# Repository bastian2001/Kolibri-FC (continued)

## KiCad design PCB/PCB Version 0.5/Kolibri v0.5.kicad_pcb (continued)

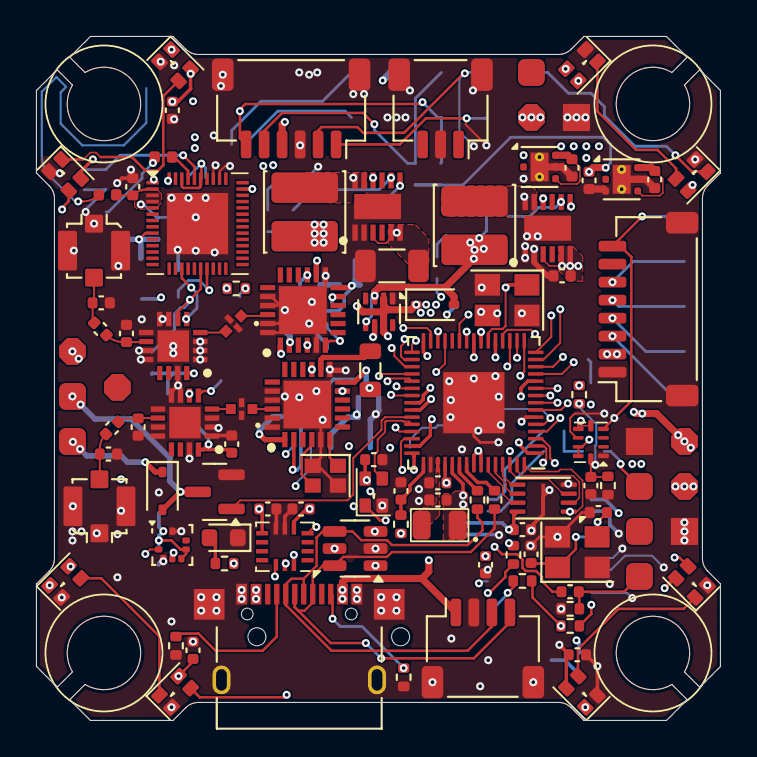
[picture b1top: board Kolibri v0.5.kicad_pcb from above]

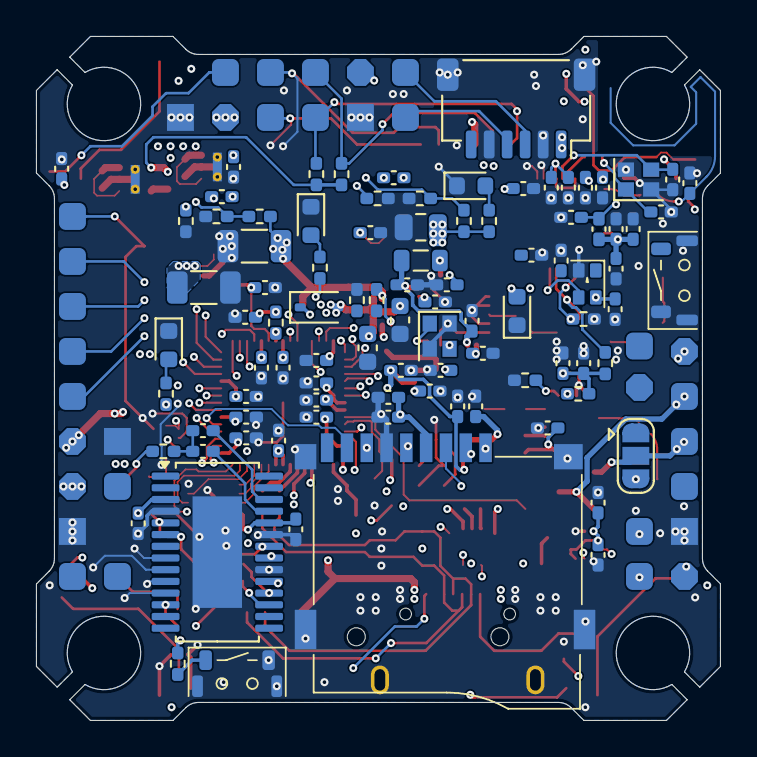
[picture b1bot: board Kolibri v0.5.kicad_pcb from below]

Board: 8 copper layers, 38.0 x 38.0 mm, 216 parts (114 on the bottom side), 144 nets.

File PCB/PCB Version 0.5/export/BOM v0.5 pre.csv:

Reference,Value,LCSC #,Datasheet,Footprint,Qty,DNP
"C1,C3,C4,C5,C6,C7,C8,C9,C10,C16,C17,C18,C19,C20,C21,C22,C23,C24,C25,C26,C27,C28,C33,C34,C40,C44,C45,C60,C62,C65,C67,C70,C71,C74,C76,C85,C86",100n,C110251,~,Capacitor_SMD:C_0402_1005Metric,37,
"C2,C11,C12,C13",4.7u,C368809,~,Capacitor_SMD:C_0402_1005Metric,4,
"C14,C15,C38,C39,C79,C80",15p,C880657,~,Capacitor_SMD:C_0402_1005Metric,6,
"C29,C30,C35,C50,C53,C73,C75,C81,C82,C83,C84",1u,0402 + 0603 alles da,~,Capacitor_SMD:C_0402_1005Metric,11,
"C31,C42,C43,C55,C56",10n,0402 + 0603 alles da,~,Capacitor_SMD:C_0402_1005Metric,6,
"C32,C37",1.5p,C76958,~,Capacitor_SMD:C_0402_1005Metric,2,
"C36,C77,C78",10u,ist da,~,Capacitor_SMD:C_0402_1005Metric,3,
"C41,C61",470n,ist da,~,Capacitor_SMD:C_0402_1005Metric,2,
"C46,C57",47p,ist da,~,Capacitor_SMD:C_0402_1005Metric,2,
"C49,C54",220p,C7503514,~,Capacitor_SMD:C_0402_1005Metric,2,
"C51,C52,C58,C59",DNF,-,~,Capacitor_SMD:C_0402_1005Metric,4,
"C63,C64",1u,0402 + 0603 alles da,~,Capacitor_SMD:C_0603_1608Metric,2,
C66,47u,ist da,~,Capacitor_SMD:C_1206_3216Metric,1,
"C68,C69",2.2u,ist da,~,Capacitor_SMD:C_0805_2012Metric,2,
C72,22u,C602037,~,Capacitor_SMD:C_0805_2012Metric,1,
"D1,D2,D3,D4,D5,D6,D7,D8,D9,D11",~,30x C5349954,https://www.lcsc.com/datasheet/lcsc_datasheet_2410121315_XIN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,Kolibri custom:WS2812B_1615,10,
"D10,D12,D13",1N4148WS,C917117,https://www.vishay.com/docs/85751/1n4148ws.pdf,Diode_SMD:D_SOD-323,3,
"FL1,FL2",2450FM07D0034T,"Muss geklaut werden: C2917726, C6054595, C2651081",https://www.mouser.co.uk/datasheet/2/611/2450FM07D0034-1375634.pdf,SamacSys_Parts:2450FM07D0034T,2,
"IC1,IC3",SX1280IMLTRT,ist da,https://datasheet.datasheetarchive.com/originals/distributor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,SamacSys_Parts:QFN50P400X400X100-25N-D,2,
"IC2,IC4",RFX2401C,AT2401 ist da,,SamacSys_Parts:QFN50P300X300X60-17N-D,2,
"IC5,IC6",LMR38025SDRRR,ist da,https://www.ti.com/lit/ds/symlink/lmr38025.pdf?ts=1711363220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,SamacSys_Parts:SON50P300X300X80-13N,2,
J1,USB_C_Receptacle_USB2.0_16P,10x C963217,https://www.usb.org/sites/default/files/documents/usb_type-c.zip,Kolibri custom:USB-C SMD+THT,1,
J2,Conn_01x04_MountingPin,C2905006,~,Connector_JST:JST_SH_SM04B-SRSS-TB_1x04-1MP_P1.00mm_Horizontal,1,
"J3,J4",Conn_Coaxial_Small,C5137195,~,Connector_Coaxial:U.FL_Molex_MCRF_73412-0110_Vertical,2,
J5,Conn_01x08_MountingPin,C7433429,~,Connector_JST:JST_SH_SM08B-SRSS-TB_1x08-1MP_P1.00mm_Horizontal,1,
"J6,J7",Conn_01x06_MountingPin,ist da,~,Connector_JST:JST_SH_SM06B-SRSS-TB_1x06-1MP_P1.00mm_Horizontal,2,
J8,Conn_01x03_MountingPin,C7433424,~,Connector_JST:JST_SH_SM03B-SRSS-TB_1x03-1MP_P1.00mm_Horizontal,1,
J9,Micro_SD_Card_Det1,ist da,https://datasheet.lcsc.com/lcsc/2110151630_XKB-Connectivity-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,Kolibri custom:Micro SD Card (TF),1,
L1,3.3u,C42411119,~,,1,
L2,2.0n,ist da,~,Inductor_SMD:L_0402_1005Metric,1,
L3,3.0n,ist da/s.u.,~,Inductor_SMD:L_0402_1005Metric,1,
L4,24n,C401493,~,Inductor_SMD:L_0402_1005Metric,1,
"L5,L6",15u,C5344252,~,Inductor_SMD:L_0402_1005Metric,2,
"L7,L8",4.7u,C520275,~,Inductor_SMD:L_Cenker_CKCS4020,2,
"P1,P2,P3,P4,P5,P6,P7,P8,P9,P10,P11,P12,P13,P14,P15,P16,P17",~,-,,Kolibri custom:Solder_Pad_rounded,17,
"P18,P19,P20,P21,P22",~,-,,Kolibri custom:Solder_Pad_rounded_dual,5,
"P23,P24,P25",~,-,,Kolibri custom:Solder_Pad_rect_dual,3,
"P26,P27",~,-,,Kolibri custom:Solder_Pad_rect,2,
"P28,P29,P30,P33,P34",~,-,,Kolibri custom:Solder_Pad_octa_dual,5,
"P31,P32",~,-,,Kolibri custom:Solder_Pad_octa,2,
Q1,BSS138,100x C5224263,https://www.onsemi.com/pub/Collateral/BSS138-D.PDF,Package_TO_SOT_SMD:SOT-23,1,
"R1,R2",27,0402 + 0603 alles da,~,Resistor_SMD:R_0402_1005Metric,2,
R3,33,C138002,~,Resistor_SMD:R_0402_1005Metric,1,
"R4,R21,R22,R23",1k,0402 + 0603 alles da,~,Resistor_SMD:R_0402_1005Metric,4,
"R5,R6",5.1k,0402 + 0603 alles da,~,Resistor_SMD:R_0402_1005Metric,2,
"R7,R8",6.8k,C2906876,~,Resistor_SMD:R_0402_1005Metric,2,
"R9,R10,R11,R12,R13",100k,0402 ist da,~,Resistor_SMD:R_0402_1005Metric,5,
R14,39k,C328318,~,Resistor_SMD:R_0402_1005Metric,1,
R15,40.2k,C2933097,~,Resistor_SMD:R_0402_1005Metric,1,
"R16,R20,R27",10k,0402 + 0603 alles da,~,Resistor_SMD:R_0402_1005Metric,3,
R17,22.6k,C321379,~,Resistor_SMD:R_0402_1005Metric,1,
R18,21.5k,0402 ist da,~,Resistor_SMD:R_0402_1005Metric,1,
R19,90.9k,0402 ist da,~,Resistor_SMD:R_0402_1005Metric,1,
"R24,R25",75,0402 + 0603 alles da,~,Resistor_SMD:R_0402_1005Metric,2,
R26,120k,-> 100k,~,Resistor_SMD:R_0402_1005Metric,1,
S1,Goertek SPL06-001,-> 3x C94049 (STMicro),,Kolibri custom:Goertek SPL06-001,1,
U1,RP2350A,10x C42411118,,Kolibri custom:QFN-60_EP_7x7_Pitch0.4mm,1,
U2,BMI270,2x C2836813,https://www.bosch-sensortec.com/media/boschsensortec/downloa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,Package_LGA:Bosch_LGA-14_3x2.5mm_P0.5mm,1,
U3,ESP32-U4WDH,2x C20622217,,Kolibri custom:QFN-48_EP_5x5_Pitch0.35mm,1,
U4,TPS2116DRL,ist da,https://www.ti.com/lit/ds/symlink/tps2116.pdf,Package_TO_SOT_SMD:SOT-583-8,1,
U5,AT7456E,10x C82351,,Package_SO:HTSSOP-28-1EP_4.4x9.7mm_P0.65mm_EP2.75x6.2mm,1,
U6,LP5912-3.3DRV,ist da,http://www.ti.com/lit/ds/symlink/lp5912.pdf,Package_SON:WSON-6-1EP_2x2mm_P0.65mm_EP1x1.6mm_ThermalVias,1,
U7,TPS746-3.3DRV,ist da,http://www.ti.com/lit/ds/symlink/lp5912.pdf,Package_SON:WSON-6-1EP_2x2mm_P0.65mm_EP1x1.6mm_ThermalVias,1,
U8,WE-TVS-824015043,ist da: C5380470,https://www.we-online.com/components/products/datasheet/8240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,Package_TO_SOT_SMD:SOT-23-6,1,
U9,TLV9002S_RUG_X2QFN,ist da,,Kolibri custom:Texas_X2QFN_RUG_10pin_1.5x2mm,1,
U10,W25Q16JVUXIQ,10x C2843335,http://www.winbond.com/resource-files/w25q32jv%20revg%200327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,Package_SON:Winbond_USON-8-1EP_3x2mm_P0.5mm_EP0.2x1.6mm,1,
"Y1,Y4",Crystal_GND24,s.u.,~,Crystal:Crystal_SMD_3225-4Pin_3.2x2.5mm,2,
Y2,Crystal_GND24,s.u.,~,Crystal:Crystal_SMD_2016-4Pin_2.0x1.6mm,1,
Y3,YXC OW7EL89CENUNFAYLC-52M,s.u.,https://www.sitime.com/support/resource-library/datasheets/s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,Oscillator:Oscillator_SMD_SiT_PQFN-4Pin_2.0x1.6mm,1,
,,,,,,
,,,,,,
,Crystals,,,,,
,12MHz 2520,C7294610,,,,
,Abra 12MHz 3225,C20625731,,,,
,27MHz 3225 von V2,C5261177,noch da,,,
,27Mhz 2016 Test,C18214311,,,,
,52MHz,C3034316,,,,
,40MHz,C37635335,,,,
,,,,,,
,,,,,,
,,,,,,
,Murata Inductor Pi,C703121,,,,
,Murata Coupling Cap,C77177,,,,
,Button,C530669,noch da,,,

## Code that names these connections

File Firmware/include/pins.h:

#include "typedefs.h"

#define PIN_TX0 0 // UART0 / Serial1
#define PIN_RX0 1 // UART0 / Serial1
#define PIN_TX1 8 // UART1 / Serial2
#define PIN_RX1 9 // UART1 / Serial2
#define PIN_TX2 10 // SoftwareSerial
#define PIN_RX2 11 // SoftwareSerial

#define PIN_OSD_MISO 12
#define PIN_OSD_CS 13
#define PIN_OSD_SCLK 14
#define PIN_OSD_MOSI 15

#define PIN_GYRO_INT1 16
#define PIN_GYRO_CS 17
#define PIN_GYRO_SCLK 18
#define PIN_GYRO_SDX 19

#define PIN_SD_DAT 2
#define PIN_SD_CMD 6
#define PIN_SD_SCLK 7

#define PIN_SDA0 24
#define PIN_SCL0 25

#define PIN_ADC_CURRENT 28
#define PIN_ADC_VOLTAGE 29

#define PIN_MOTORS 20 // pin at which the motor outputs start

#define PIN_SPEAKER 26
#define PIN_LEDS 27

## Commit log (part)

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2025-08-05 basic in flight tuning
2025-08-05 minor changes to OSD related classes
2025-08-05 basic working "OSD"
2025-08-05 nicer D gain shift
2025-08-06 math eval in numeric input
2025-08-06 German compatibility
2025-08-06 could not merge these...
2025-08-06 more debugging, doesn't work
2025-08-07 fix some things that were wrong with the return-to-x merge
2025-08-07 gyro at 400Hz
2025-08-07 fix speaker chirp
2025-08-11 get some intervals in order
2025-08-12 wip separation
2025-08-13 wip, to be tested
2025-08-13 semi-fix for blocked writes and disarm reason
2025-08-14 gen pidsum
2025-08-14 setpoint smoothing for lower control frequency
2025-08-18 store blackbox disarm reason
2025-08-18 Added more OSD elements; ready for testing
2025-08-18 !Disable Bidirectional DShot temporarily
    Because BL32 stupid doesn't allow update firmware
2025-08-28 minimize erase, write, read and init delays
    AM32 Configurator's timeouts regularly hit and made flashing impossible
    Resetting still hits the timeout
2025-08-28 voltage display with decimals
2025-08-29 remove logging duration
2025-08-29 More Blackbox elements (#109)
    Added the following blackbox items
    - Battery voltage whenever it is sampled (10Hz)
    - PID sum (can also be generated)
    - RC link statistics (RSSI etc.) whenever a Link statistics packet is received (usually 10Hz)
    simplified the leBytesToInt and leBytesToBigInt functions significantly so .slice is no longer needed
2025-08-31 wip untested
2025-09-10 Motor remapping (#114)
    - New setting to store the pins of the motors
    - 2 new MSP commands: SET/GET_MOTOR_LAYOUT (data: pins)
    - Remapping Wizard in the configurator
2025-09-11 wip working
    still need to implement retries, and change most components
2025-09-12 implement JS promises everywhere
    *where it is feasible, also omitting Blackbox for now
2025-09-12 promised blackbox
2025-09-13 fix elrs link stats recording
2025-09-13 fix blackbox file info display
2025-09-13 document JS sendCommand function
2025-09-13 JS promises for MSP commands (#116)
    sendCommand features a proper promise system now:
    - All the following parameters are adjustable
    - resolves when a packet with the same command is returned (custom function for checking returned packets possible to help with e.g. ping sequence numbers)
    - times out after 700ms
    - 3 attempts
    - internal data can be attached to the command, that the callback functions get passed, e.g. ping start time so that multiple pings don't jam up
2025-09-13 PID Boost OSD indicator
2025-09-13 Remove PIO speaker...
    it's been too long...
2025-09-13 finish removing speaker
2025-09-13 Clean up, remove PIO speaker (#118)
2025-09-13 Dump previous Tramp work
2025-09-15 wip tramp
2025-09-22 Tramp WIP
2025-09-23 hd -> hdx
2025-09-23 some light gui
2025-09-24 set frequency in configurator
2025-09-24 tunable by remote
2025-09-24 fix tuning initialize
2025-09-26 stronger background blue
2025-09-26 restyling header, better log scroll
2025-09-26 clean up home page slightly
2025-09-26 separate rate lines
2025-09-27 cargo update
2025-09-27 "fixing" something aka. compiler mimimi
2025-09-27 Configurator tweaks (#120)
    - some restyling
    - some code cleanup
    - update dependencies
2025-09-27 remove some hardware-only datasheets
2025-09-27 Move PCBs to separate Repo (#121)
2025-10-04 revert non-bidir
2025-10-04 make GPS work again
2025-10-15 IMU and Control lower update rate (#123)
    Reduces the update rate of IMU and control functions to 400Hz each. Also separates the control code into its own file for easier readability and maintenance.
2025-11-06 Implemented functions to save and load OSD configs from LittleFS
2025-11-11 making dependabot happy
2025-11-12 subframe wheel zooming and moving
2025-11-12 break out parsing into separate functions
2025-11-12 include offsets in loadedLog
2025-11-12 subframe touch move and zoom (untested)
2025-11-12 add control byte to sync
2025-11-12 wip header and data request
2025-11-15 reboot to bootloader on rightclick disconnect
2025-11-16 finished fast init and fast data req
    TODO JS scheduling
2025-11-16 wip, it opens start and end frame only for now
2025-11-16 working?
2025-11-16 removed a bunch of printf and sleeps
2025-11-17 blackbox viewer works
2025-11-18 export incomplete log with interpolation
2025-11-18 better selective drawing, motor output/RPM export
2025-11-18 Revise README for configurator updates
    Removed hardware features list and updated descriptions for various configurator features.
2025-11-18 make sync freq configurable
2025-11-18 Accelerated blackbox view (#124)
    - SYNC frames
    - polling individual frames
    - on demand download of blackbox log
    - export incomplete log by interpolating
    - show loading progress in configurator
2025-11-21 merged main into msp-displayport
2025-11-27 reading settings instead of hardcoded osd configuration
2025-11-29 wip icm implementation
2025-12-02 basic flash stuff
2025-12-03 FS creation
2025-12-04 more FS development, completely untested
2025-12-12 fix eraseBlock
2025-12-15 wip more static
2025-12-19 V0.6 implementation (#127)
    It's not all ideal, but it works generally. Kinda need this in other branches.
    - Barometer not further investigated, but doesn't work (probably hardware defect).
    - ABV still crashes the system sometimes (probably something wrong in the seek or read function of FlashFile)
    - code not completely refactored for 8kHz (PID gains, function splitting, etc.)
2025-12-19 clean up, fix MSP mix up
2025-12-27 some axes mixing around, untested
    most definitely some weird axes
2026-01-03 imu alignment mostly done
    todo accel part in imu fusion
2026-01-03 some fixing
2026-01-03 gyro only works
2026-01-03 wip (maybe working?)
2026-01-04 fix yaw jump at boot
    wait up to 50 ms to get a valid sample from the gyro
2026-01-04 simplified quaternion normalization
2026-01-04 I hate quaternions
    TODO optimization (like before)
2026-01-04 respect imu alignment during accel calibration
2026-01-05 optimizing IMU
    bench test yields 7.5-8.5 us per PID cycle now
2026-01-06 Fix sensor page interval
    Still crashing the browser sometimes. Maybe something with transferToOffscreen?
2026-01-06 adjust vAccel to new system
2026-01-06 fix when deleting a graph that was not the last
2026-01-06 UI for IMU alignment/accel calibration
2026-01-06 fix gyro calibrated flag not clearing
2026-01-07 Configurable gyro orientation (#128)
    Features:
    - Gyro/Accel axes can be configured in software now
    - Added Hardware Setup page for setting up which hardware is available and how it is connected/attached to the quad
    Improvements:
    - faster and less janky IMU code
    - more robust accel/gyro calibration routine
2026-01-07 fix some more small errors
    - speaker clock div
    - isActive for inFlightTuning fixed
2026-01-13 some hardware discovery
2026-03-11 remove crash log
    RP2350 does not have uninitialized ram
2026-03-11 adjust for 4.0, fix zero length packets
2026-03-13 rather basic ELRS configuration
2026-03-13 improved fetching order and UI
2026-03-13 removed serial print for some commands
2026-03-13 string handling (still untested), cleanup
    nothing uses strings, so I cannot test
2026-03-13 corrected visual oopsie
2026-03-15 working on configurable serial ports
2026-03-16 working pio serial, now doing dma
2026-03-16 SerialPioHdx RX DMA Buffer
2026-03-16 fix boot order
2026-03-17 wip configurable serial
2026-03-18 More configurability
2026-03-20 finished configurability
2026-03-20 recommended and allowed pins, pin labels
2026-03-20 Serial port configuration (#131)
    * configurable serial ports
    * some hardware discovery
    * motor state in hardware setup
    * DMA RX buffer for PIO based serials
    * updated Readme
2026-03-21 default button
2026-03-21 Package updates (#132)
    * npm and cargo updates
    * default button
2026-03-22 more OSD work
2026-03-23 finalizing main merge
2026-03-23 wip compilable
2026-03-25 making Thernu happy
    I even used proper Singletons
2026-03-25 remove old implementation
2026-03-26 make MSP DP work (at least on Walksnail)
2026-03-26 remove betaflight compatibility mode
2026-03-26 fixed oopsie
2026-03-28 implemented negative column support for OSD added a few OSD-Elements, ready for testing
2026-03-28 better selection highlight in log
2026-04-02 Basic warnings and RC setpoints
2026-04-02 Example text should show spacing correctly now
2026-04-12 aspect ratio for preview
2026-04-13 separate style into main.css
2026-04-13 fixed some fuckups
2026-04-14 drag and drop hints in OSD
2026-04-14 improved some OSD elements
2026-04-15 MSP DP online indicator
2026-04-15 better canvas size setting
2026-04-18 home direction arrow, better ESC temp
2026-04-18 reworked RC channels
2026-04-19 custom text element
2026-04-19 OSD preview in configurator
2026-04-19 throttling MSP_DP over CRSF to prevent RX crashes
2026-04-19 default live preview off
2026-04-19 fix buggy browser
    Apply opacity to lower element and it works less clunky wtf
2026-04-20 port commands over to new system
2026-04-20 cleanup
2026-04-20 better tab and CR support
2026-04-20 cooler gyro calibration with a spinner
2026-04-20 fixing exceptions
2026-04-21 more CLI control characters
2026-04-21 bugfix
2026-04-21 improved man
2026-04-21 some syntax highlighting
2026-04-24 reincarnate upload.js
2026-05-06 CLI suggestions
    not completely finished yet
2026-05-06 user flow improvement
2026-05-06 Command class (#135)
    A pretty much entire CLI overhaul
    - colorized text
    - \r, \b and other control characters for a more complex command interaction flow with fullscreen interfaces and different colors
    - asynchronous command operation while the FC is doing other things (.loop(), .input())
    - commands as a class with generic parameter parsing
    - man page automatically generated
2026-05-07 fixed cli oopsie
2026-05-08 updated packages
2026-05-09 add license to configurator
2026-05-10 optimize CLI lol
2026-05-10 configurator OSD multiline support
2026-05-10 clean up unicode chars with regular hex chars
2026-05-14 wip but seems to work
2026-05-17 fix oopsie Serial.printf
2026-05-17 move diffQuat inversion to runAngleMode4
2026-05-17 get alignment in configurator
2026-05-17 volatile blackbox flags, cache result
2026-05-26 MSP Displayport (HD OSD) (#134)
    first part of MSP DP
    - an entirely new OSD backend and drawing mechanism
    - frame buffer that is drawn to
    - frame buffer pushed to all enabled outputs
    - an OSD page in the configurator that is actually useful
    - Configurable OSD elements, finally
2026-05-26 simple OSD comparison
2026-05-26 call task
2026-05-27 maybe fixed issue
2026-05-29 a lot of debugging
2026-05-29 remove debugging measures
2026-05-29 MSP Displayport part 2 (#137)
2026-06-02 decrease analog OSD SPI transfer duration
    - some setup, and then only one SPI byte per OSD char
    - the AT7456E/MAX7456 sucks
2026-06-03 Analog OSD speedup (#139)
    Massive speed improvements for analog OSD
    - instead of 6 bytes per character, now it only transfers one byte
    - smaller chunks of data, thus lower jitter
2026-06-06 improve readability
2026-06-07 prevent fetching of e.g. GPS when there is no GPS
    live loading would fail if there was e.g. no GPS recorded but requested. Similarly for VBAT or ELRS
2026-06-07 remove unnecessary logs
2026-06-07 Fix live loading (#140)
    Loading a blackbox with the live option sometimes failed. I crushed two bugs:
    - Sync frequency was set to 0 whenever you updated the blackbox flags, it was unintentionally not sent nor saved
    - The special frames, i.e. GPS, ELRS..., were always requested, even when they were not recorded. There is now a catch on the FC side that sends an error in these cases, and the configurator is now s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
2026-06-07 Mutex for RC channels (#141)
    Prevents (or rather tries to prevent – there are timeouts) rare glitches (caused by race condition) on the smoothed channels
2026-06-07 better RX lost handling
2026-06-07 ooooopsie
